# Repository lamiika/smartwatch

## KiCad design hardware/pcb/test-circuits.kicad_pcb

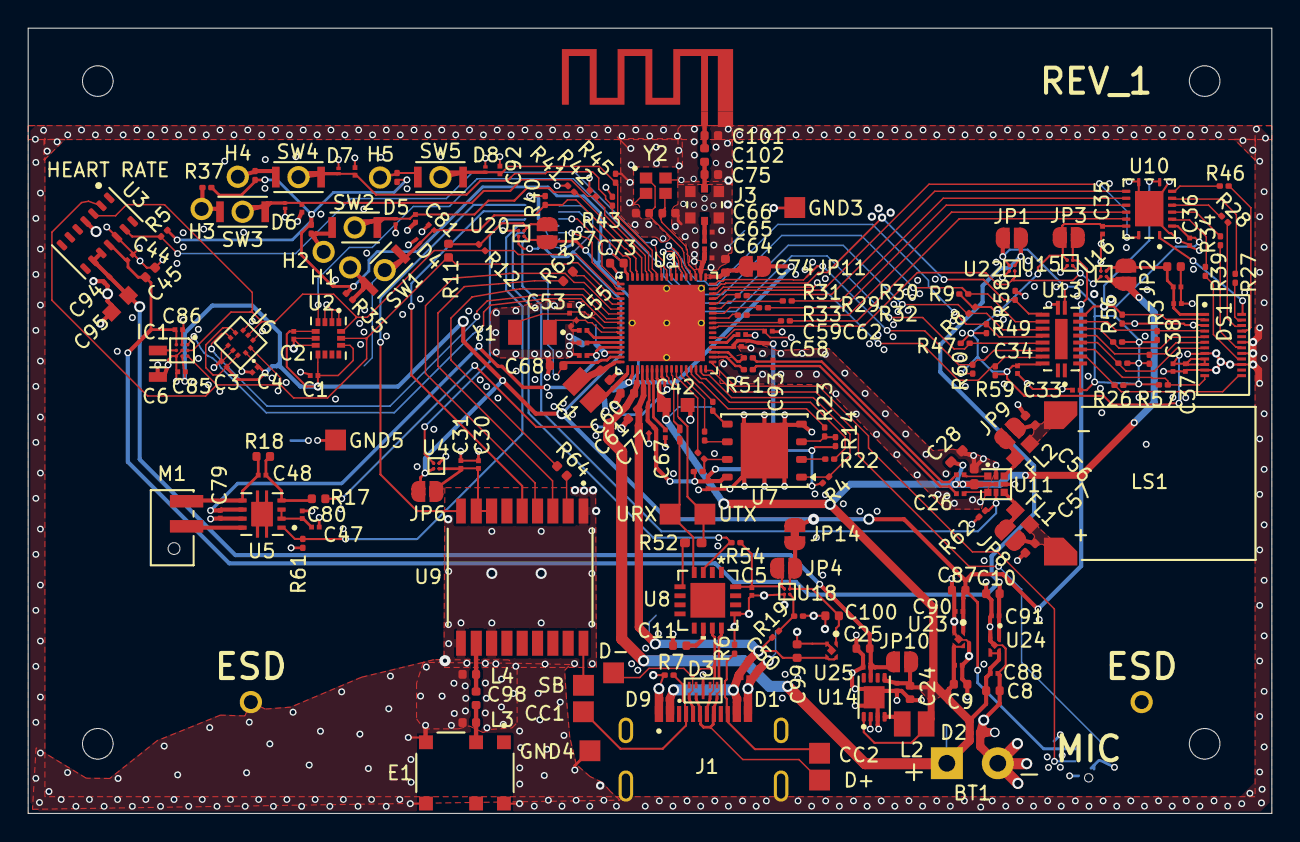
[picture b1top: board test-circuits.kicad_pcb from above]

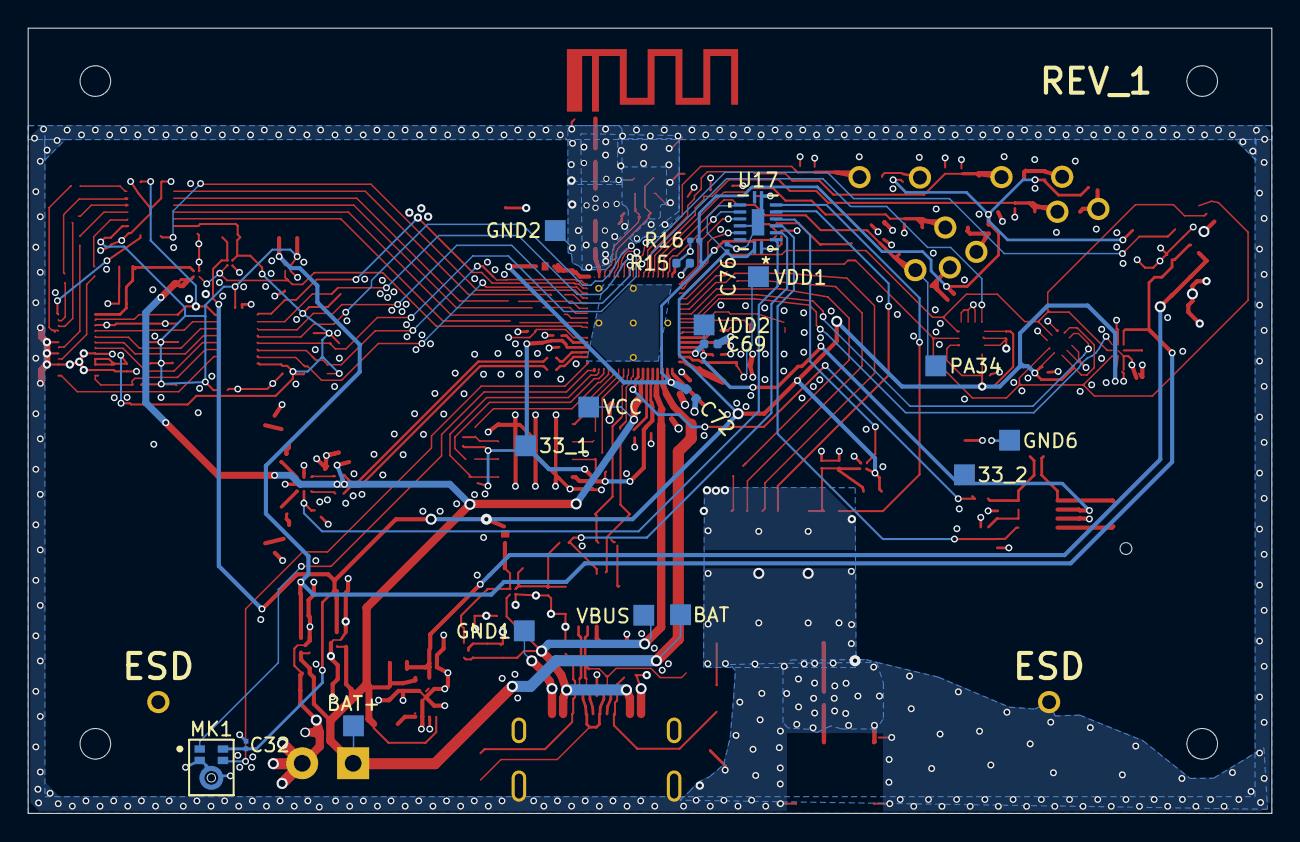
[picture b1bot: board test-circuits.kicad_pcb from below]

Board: 4 copper layers, 89.3 x 56.4 mm, 242 parts (20 on the bottom side), 146 nets.

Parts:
33_1, 33_2: TestPoint_Square; TestPoint_Pad_1.5x1.5mm
BAT: TestPoint_Square; TestPoint_Pad_1.5x1.5mm
BAT+: TestPoint_Square; TestPoint_Pad_1.5x1.5mm
BT1: Battery_Cell; Battery_LiPo_wire_leads
C1, C2, C5, C23, C30, C33, C34, C35, C36, C37, C38, C39, C44, C49, C76, C77, C78, C79, C81, C82, C83, C84, C92: 100nF_0201; C_0201_TightCourtyard
C3, C4: 100n; C_0201_TightCourtyard
C6: 2.2uF_0402_6.3V; C_0805
C8, C9, C10, C87, C99, C100: 1uF_0402_25V; C_0402
C11: 0.22uF; C_0402_1005Metric
C24, C25: 10uF 0402 X7R; C_0402_1005Metric
C26, C27: 1nF_0201_4V; C_0201_TightCourtyard
C28: 10u; C_0402_1005Metric_Pad0.74x0.62mm_HandSolder
C29: 1u; C_0402_1005Metric_Pad0.74x0.62mm_HandSolder
C31, C32, C41, C59, C62, C71: 1uF_0201_4V; C_0201_TightCourtyard
C40, C45, C46, C68, C69, C72, C73, C74: 4.7uF_0402_6.3V; C_0402
C42, C95: 10uF_0603_10V; C_0603
C47, C48: 10nF_0201; C_0201_TightCourtyard
C50, C61: 10uF; C_0402_1005Metric
C52, C54: 1.2pF; C_0402_1005Metric
C53, C55: 1.2pF; C_0201_TightCourtyard
C56, C57: 200pF; C_0402_1005Metric
C58, C67: 2.2uF_0201_10V; C_0201_TightCourtyard
C60: 4.7uF_0402_10V; C_0402
C64, C65, C66: 15pF_0201; C_0201_TightCourtyard
C70: 470nF; C_0201_TightCourtyard
C75, C101, C102: 15pF_0201; C_0402
C80: 1nF_0201; C_0201_TightCourtyard
C85, C86, C94, C96, C97: 100nF_0201_X7R; C_0201_TightCourtyard
C88, C89, C90, C91: 100nF_0201_X0G; C_0201_TightCourtyard
C93: 1.5nF_0201; C_0201_TightCourtyard
C98: 1.5pF_0402_50V; C_0402
CC1, CC2: TestPoint_Square; TestPoint_Pad_1.5x1.5mm
D1, D2, D4, D5, D6, D7, D8, D9: ESD_BD_CL6.5pF; ESD200_B1_CSP0201
D3: PUSB3BB4; PUSB3BB4_DFN2510A10
D+: TestPoint_Square; TestPoint_Pad_1.5x1.5mm
D-: TestPoint_Square; TestPoint_Pad_1.5x1.5mm
DS1: GLO132-D-M2003; GLO132-D-M2003_OK-03F024-04
E1: SR4G008; XCVR_SR4G008
ESD: MountingHole_Pad_1.0mm; TH_1.0mm_Pad1.6mm
ESD#2: MountingHole_Pad_1.0mm; TH_1.0mm_Pad1.6mm
FL1, FL2: BLM18PG121SN1D; BEADC1608X95N
GND1, GND2, GND3, GND4, GND5, GND6: TestPoint_Square; TestPoint_Pad_1.5x1.5mm
H1, H2, H3, H4, H5: MountingHole_Pad_1.2mm; TH_1.0mm_Pad1.6mm
IC1: BMM350; BGA9C40P3X3_128X128X54
J1: UJ20-C-H-G-MSMT-2B-P16-TR; SAMESKY_UJ20-C-H-G-MSMT-2B-P16-TR
J3: MM8130-2600RA2; MURATA_MM8130-2600RA2
JP1, JP2, JP3, JP4, JP6, JP7, JP8, JP9, JP10: SolderJumper_2_Open; SolderJumper-2_P1.3mm_Open_RoundedPad1.0x1.5mm
JP11, JP14: SolderJumper_2_Bridged; SolderJumper-2_P1.3mm_Bridged_RoundedPad1.0x1.5mm
L1, L2: MLP2016H4R7MT0S1; INDC2016X100N
L3, L4: 12nH; 0402
LS1: CMS-151125-18S-X8; SPKR_CMS-151125-18S-X8
M1: Motor_AC; VLV041235L
MK1: IM68D121JV01XTMA1; IFX-PG-TLGA-5N-9-V
PA34: TestPoint_Square; TestPoint_Pad_1.5x1.5mm
R3, R8, R9, R13: res_2.2k_0201; R_0201_0603Metric
R4, R10, R14, R19, R25, R26, R47, R48, R49, R56, R57, R58, R59, R60, R61, R62: 100k_0201; R_0201_0603Metric
R5, R16, R40, R41, R42, R43, R45, R54: 10k_0201; R_0201_0603Metric
R6, R7, R35, R36, R37, R38, R44: 5.1k_0201; R_0201_0603Metric
R11: 2.2k_0402; R_0402
R12: 2.2k_0201; R_0201_0603Metric
R15: 10k; R_0402
R17: 100k_0402; R_0402
R18: 68k_0402; R_0402
R20: 1M_0201; R_0201_0603Metric
R21, R22, R23, R24, R55: 33R_0201; R_0201_0603Metric
R27, R28, R34, R39, R46: 0R_0201; R_0201_0603Metric
R29, R30, R31, R32, R33: 100R_0201; R_0201_0603Metric
R50, R51: 1.0k_0201; R_0201_0603Metric
R52: 100R_0201; R_0402_1005Metric_Pad0.72x0.64mm
R53: 100R_0201; R_0201_0603Metric_Pad0.64x0.40mm
R63, R64: 33R_0402; R_0402
SB: TestPoint_Square; TestPoint_Pad_1.5x1.5mm
SW1, SW2, SW3, SW4, SW5: TL3780AF100QG; TL3780AF100QG-through-holes
U1: SF32LB52xUx; ArtInChip_0.2_QFN-68-1EP_7x7mm_P0.35mm_EP5.49x5.49mm
U2: LSM6DSV16XTR; XDCR_LSM6DSV16XTR
U3: MAX30101EFD; PSON80P560X330X165-14N
U4, U15, U16, U18, U20, U22: TCK127BG_LF; WCSP4G_TOS
U5: DRV8601DRBR; IC_DRV8601DRBT
U6: BMP581
U7: XT25F128FWOIGT-W; WSON-8-1EP_6x5mm_P1.27mm_EP3.4x4mm
U8: MCP2221A-I/ML; QFN16_ML_MCH
U9: MAX-M10M-00B; XCVR_MAX-M10M-00B
U10: TXB0606RGYR; VQFN-16_RGY0016A_TEX
U11: PAM8013AKR
U13: NXS0108BQX; IC_NXS0108BQX
U14: DIO6605BFN8; DIO6605BFN8_DFN2x3_8EP
U17: 74HC595BQ,115; DHVQFN16_SOT763-1_NEX
U23, U25: MIC5317-3.3YMT-TZ; VREG_MIC5317-3.3YMT-TZ
U24: MIC5365-1.8YMT-TZ; VREG_MIC5365-1.8YMT-TZ
URX: TestPoint_Square; TestPoint_Pad_1.5x1.5mm
UTX: TestPoint_Square; TestPoint_Pad_1.5x1.5mm
VBUS: TestPoint_Square; TestPoint_Pad_1.5x1.5mm
VCC: TestPoint_Square; TestPoint_Pad_1.5x1.5mm
VDD1, VDD2: TestPoint_Square; TestPoint_Pad_1.5x1.5mm
Y1: SF32K32768D71T01; SF32K32768D71T01_3215
Y2: SX20Y048000B31T004; SX20Y048000B31T004_2016

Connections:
+1V8: C10.1, C44.1, C45.1, C86.2, C91.1, IC1.C1 (VDD), JP1.2 (B), U3.11 (VDD), U22.A2 (VIN), U24.1 (VOUT)
+3V3: C1.1, C2.1, C3.1, C4.1, C32.2, C76.2, C85.2, C87.1, C90.1, IC1.B3 (VDDIO), JP3.2 (B), JP6.2 (B), JP14.2 (B), MK1.5 (VDD), U2.5 (VDD_IO), U2.8 (VDD), U2.12 (CS), U4.A2 (VIN), U6.1 (VDDIO), U6.6 (CSB), U6.10 (VDD), U15.A2 (VIN), U17.10 (*MR), U17.16 (VCC), U23.1 (VOUT)
/Connector/3V3: C100.1, JP4.2 (B), JP14.1 (A), U18.A2 (VIN), U25.1 (VOUT)
/Connector/D+: D3.2 (CH2), D3.5 (CH4), D+.1 (1_1), J1.A6 (DP1), J1.B6 (DP2), U8.12 (D+)
/Connector/D-: D3.1 (CH1), D3.4 (CH3), D-.1 (1_1), J1.A7 (DN1), J1.B7 (DN2), U8.11 (D-)
/Connector/DBG_*RST: R54.2, U8.3 (*RST), U17.3 (Q3)
/Connector/DBG_UART_RXD: R53.2, U8.4 (URX), URX.1 (1_1)
/Connector/DBG_UART_TXD: R52.1, U1.27 (PA18), UTX.1 (1_1)
/Connector/VDD: C5.2, JP4.1 (A), R54.1, U8.16 (VDD), U18.A1 (VOUT)
/Display Module/1V8_circuit: C33.2, C36.2, JP1.1 (A), R3.1, R13.1, R25.1, R26.2, R48.1, R57.2, U10.2 (VCCA), U13.2 (VCC_A), U13.10 (OE), U22.A1 (VOUT)
/Display Module/3V3_circuit: C34.2, C35.2, C37.1, C38.1, DS1.9 (VDD33), DS1.10 (VDD33), JP3.1 (A), R8.1, R9.1, R47.1, R49.1, R59.2, R60.2, U10.15 (VCCB), U13.19 (VCC_B), U15.A1 (VOUT)
/Display Module/DISPLAY_SI00: R30.2, U1.46 (PA5)
/Display Module/DISPLAY_SI01: R29.2, U1.45 (PA6)
/Display Module/DISPLAY_SI02: R33.2, U1.44 (PA7)
/Display Module/DISPLAY_SI03: R32.2, U1.43 (PA8)
/Display Module/DISPLAY_SPI_CLK: R31.2, U1.47 (PA4)
/Display Module/DISPLAY_SPI_CS: U1.48 (PA3), U10.16 (B1)
/Display Module/LOAD_DISPLAY: U1.42 (PA9), U15.B2 (CONTROL), U16.B2 (CONTROL), U22.B2 (CONTROL)
/Display Module/RESET_1V8: DS1.12 (RESET), R57.1, U13.4 (A3)
/Display Module/VCI_EN_1V8: DS1.2 (VCI_EN), R56.1, U10.8 (OE), U13.9 (A8)
/Display Module/i_INT: R47.2, U1.57 (PA43), U13.16 (B4)
/Display Module/i_RESET: R60.1, U1.51 (PA0), U13.17 (B3)
/Display Module/i_RST: R49.2, U1.56 (PA44), U13.15 (B5)
/Display Module/i_SCL: R9.2, U1.58 (PA42), U13.13 (B7)
/Display Module/i_SDA: R8.2, U1.59 (PA41), U13.14 (B6)
/Display Module/i_TE: R59.1, U1.49 (PA2), U13.18 (B2)
/Display Module/i_VCI_EN: R58.1, U1.50 (PA1), U13.12 (B8)
/Display Module/t_INT: DS1.7 (TP_INT), R25.2, U13.5 (A4)
/Display Module/t_RST: DS1.6 (TP_RST), R48.2, U13.6 (A5)
/Display Module/t_SCL: DS1.4 (TP_SCL), R3.2, U13.8 (A7)
/Display Module/t_SDA: DS1.5 (TP_SDA), R13.2, U13.7 (A6)
/Display Module/t_TE: DS1.13 (TE), R26.1, U13.3 (A2)
/Flash Storage/FLASH CS#: R4.2, U1.33 (PA12), U7.1 (CS#)
/Flash Storage/FLASH IO0: R21.2, U1.30 (PA15)
/Flash Storage/FLASH IO1: R22.2, U1.32 (PA13)
/Flash Storage/FLASH IO2: R23.2, U1.31 (PA14)
/Flash Storage/FLASH IO3: R24.2, U1.28 (PA17)
/Flash Storage/FLASH SCK: R55.1, U1.29 (PA16)
/GNSS/GNSS_EXTINT: U9.5 (EXTINT), U17.6 (Q6)
/GNSS/GNSS_RESET: U9.9 (~RESET), U17.7 (Q7)
/GNSS/GNSS_RXD: R63.1, U9.3 (RXD)
/GNSS/GNSS_TIMEPULSE: U1.6 (PA27), U9.4 (TIMEPULSE)
/GNSS/GNSS_TXD: R64.1, U1.7 (PA26)
/GNSS/LOAD_GNSS: U4.B2 (CONTROL), U17.5 (Q5)
/Heart Rate PPG/INT_PPG: R5.2, U1.60 (PA40), U3.13 (~INT)
/IMU/INT1_IMU: U1.61 (PA39), U2.4 (INT1)
/MCU/48-1: C52.1, U1.55 (XTAL48M_XI), Y2.1 (XTAL1)
/MCU/48-2: C54.1, U1.54 (XTAL48M_XO), Y2.3 (XTAL2)
/MCU/ANT: C64.1, C65.1, U1.53 (ANT)
/MCU/AVDD_BRF: C74.2, JP11.1 (A), U1.52 (AVDD_BRF)
/MCU/BT_ANT_MATCHING: C75.1, C102.1, J3.2 (OUT)
/MCU/BT_ANT_TRACE: C101.1, C102.2
/MCU/BUCK_FB: C46.2, L1.2, U1.17 (BUCK_FB)
/MCU/BUCK_LX: L1.1, U1.18 (BUCK_LX)
/MCU/CLK_MK: MK1.4 (CLK), U1.35 (PA10)
/MCU/DATA_MK: MK1.1 (DATA), U1.34 (PA11)
/MCU/DS: U1.2 (PA31), U17.14 (DS)
/MCU/GPADC_VREF: C73.2, R15.2, R16.2, U1.68 (GPADC_VREF)
/MCU/INT_BARO: U1.8 (PA25), U6.7 (INT)
/MCU/INT_MAGN: IC1.A1 (INT), U1.9 (PA24)
/MCU/LOAD_I2C_S: U17.1 (Q1), U20.B2 (CONTROL)
/MCU/LRA_EN: R61.2, U5.1 (EN), U17.4 (Q4)
/MCU/LRA_IN1: R17.1, U1.25 (PA20)
/MCU/MIC_BIAS: C62.1, U1.40 (MIC_BIAS)
/MCU/SD_SPEAKER: R62.1, U11.8 (SD), U17.2 (Q2)
/MCU/SHCP: U1.67 (PA33), U17.11 (SHCP)
/MCU/SPEAKER_N: C26.1, C93.1, R51.2
/MCU/SPEAKER_P: C27.1, C93.2, R50.2
/MCU/STCP: U1.1 (PA32), U17.12 (STCP)
/MCU/VDD18_VOUT: C67.1, U1.23 (VDD18_VOUT)
/MCU/VDD_RET: C70.1, U1.13 (VDD_RET)
/MCU/VDD_RTC: C71.1, U1.12 (VDD_RTC)
/MCU/VDD_VOUT1: C68.1, U1.16 (VDD_VOUT1), VDD1.1 (1_1)
/MCU/VDD_VOUT2: C69.1, U1.15 (VDD_VOUT2), VDD2.1 (1_1)
/MCU/dac+: R50.1, U1.37 (DACP)
/MCU/dac-: R51.1, U1.36 (DACN)
/MCU/sw1: C81.2, D4.2, PA34.1 (1_1), R40.1, SW1.1, U1.66 (PA34)
/MCU/sw2: C82.2, D5.2, R41.1, SW2.1, U1.65 (PA35)
/MCU/sw3: C83.2, D6.2, R42.1, SW3.1, U1.64 (PA36)
/MCU/sw4: C84.2, D7.2, R43.1, SW4.1, U1.63 (PA37)
/MCU/sw5: C92.2, D8.2, R45.1, SW5.1, U1.62 (PA38)
/SCL_S: IC1.A3 (SCK), R11.2, U1.4 (PA29), U2.13 (SCL), U3.2 (SCL), U6.2 (SCK)
/SDA_S: IC1.A2 (SDA), R12.2, U1.3 (PA30), U2.14 (SDA), U3.3 (SDA), U6.4 (SDI)
/Speaker/IN+: C27.2, U11.1 (INP)
/Speaker/IN-: C26.2, U11.7 (INN)
BAT: BAT.1 (1_1), BAT+.1 (1_1), BT1.1 (+), C8.1, C9.1, C24.1, C28.1, C29.1, C42.1, C60.1, C88.1, C89.1, C96.1, D2.2, JP2.2 (B), JP10.1 (A), L2.1, U1.20 (BAT), U1.24 (VCC), U11.4 (VDD), U11.5 (VDD), U14.1 (EN), U14.5 (VIN), U16.A2 (VIN), U23.3 (EN), U23.4 (VIN), U24.3 (EN), U24.4 (VIN), VCC.1 (1_1)
GND: BT1.2 (-), C1.2, C2.2, C3.2, C4.2, C5.1, C6.2, C8.2, C9.2, C10.2, C11.2, C23.2, C24.2, C25.2, C28.2, C29.2, C30.2, C31.2, C32.1, C33.1, C34.1, C35.1, C36.1, C37.2, C38.2, C39.2, C40.2, C41.2, C42.2, C44.2, C45.2, C46.1, C47.1, C49.1, C50.2, C52.2, C53.2, C54.2, C55.2, C56.1, C57.1, C58.1, C59.1, C60.2, C61.2, C62.2, C65.2, C66.2, C67.2, C68.2, C69.2, C70.2, C71.2, C72.2, C73.1, C74.1, C75.2, C76.1, C77.1, C78.1, C79.1, C80.1, C81.1, C82.1, C83.1, C84.1, C85.1, C86.1, C87.2, C88.2, C89.2, C90.2, C91.2, C92.1, C94.2, C95.2, C96.2, C97.2, C99.2, C100.2, C101.2, D1.1, D2.1, D3.3 (GND), D3.9 (GND), D4.1, D5.1, D6.1, D7.1, D8.1, D9.1, DS1.3 (GND), DS1.8 (GND), DS1.11 (GND), DS1.15 (GND), DS1.17 (GND), DS1.19 (GND), E1.3, E1.4, E1.6, ESD.1 (1_1), ESD#2.1 (1_1), GND1.1 (1_1), GND2.1 (1_1), GND3.1 (1_1), GND4.1 (1_1), GND5.1 (1_1), GND6.1 (1_1), IC1.B1 (GND), IC1.B2 (ADSEL), IC1.C3 (BYPASS), J1.A1/B12 (GND), J1.B1/A12 (GND__1), J1.SH1 (SHIELD), J1.SH2 (SHIELD__1), J1.SH3 (SHIELD__2), J1.SH4 (SHIELD__3), J3.G1 (GND), J3.G2 (GND__1), J3.G3 (GND__2), J3.G4 (GND__3), L3.1, L4.1, MK1.2 (LR), MK1.3 (GND), R6.2, R7.2, R15.1, R20.2, R40.2, R41.2, R42.2, R43.2, R45.2, R56.2, R58.2, R61.1, R62.2, U1.69, U2.1 (SDO/SA0), U2.2 (SDX/AH1/QVAR1), U2.3 (SCX/AH2/QVAR2), U2.6 (GND), U2.7 (GND), U3.4 (PGND), U3.12 (GND), U4.B1 (GND), U5.7 (GND), U6.3 (VSS_1), U6.5 (SDO), U6.8 (VSS_2), U6.9 (VSS_3), U7.4 (VSS), U7.9 (EPAD), U8.13 (VSS), U9.1 (GND), U9.10 (GND__1), U9.12 (GND__2), U10.9 (GND), U10.17 (EPAD), U11.2 (GND), U11.6 (GND), U13.11 (GND), U14.2 (AGND), U14.3 (PGND), U14.9 (GND_PAD), U15.B1 (GND), U16.B1 (GND), U17.8 (GND), U17.13 (*OE), U17.17 (GND), U18.B1 (GND), U20.B1 (GND), U22.B1 (GND), U23.2 (GND), U23.5 (EPAD), U24.2 (GND), U24.EP (EXP), U25.2 (GND), U25.5 (EPAD), Y2.2 (GND), Y2.4 (GND)
unnamed: C98.1, E1.2, L3.2
unnamed: DS1.23 (SIO0_MOSI_SDA), R27.1
unnamed: DS1.22 (SIO1_MISO), R28.1
unnamed: DS1.18 (SIO2), R34.1
unnamed: DS1.16 (SIO3), R39.1
unnamed: DS1.21 (SPI_CLK), R46.2
unnamed: DS1.24 (SPI_CS), U10.1 (A1)
unnamed: C39.1, C40.1, C41.1, DS1.1 (VBAT), JP2.1 (A), U16.A1 (VOUT)
unnamed: H1.1 (1_1), R35.2, SW1.2
unnamed: H2.1 (1_1), R36.2, SW2.2
unnamed: H3.1 (1_1), R37.2, SW3.2
unnamed: H4.1 (1_1), R38.2, SW4.2
unnamed: H5.1 (1_1), R44.2, SW5.2
unnamed: C6.1, IC1.C2 (CRST)
unnamed: CC1.1 (1_1), J1.A5 (CC1), R7.1
unnamed: CC2.1 (1_1), J1.B5 (CC2), R6.1
unnamed: C64.2, C66.1, J3.1 (IN)
unnamed: C30.1, C31.1, JP6.1 (A), U4.A1 (VOUT), U9.7 (V_IO), U9.8 (VCC)
unnamed: JP7.2 (B), R11.1, R12.1, U20.A1 (VOUT)
unnamed: C57.2, FL1.2, JP8.1 (A), LS1.P
unnamed: FL1.1, JP8.2 (B), U11.9 (OUTP)
unnamed: FL2.1, JP9.1 (A), U11.3 (OUTN)
unnamed: C56.2, FL2.2, JP9.2 (B), LS1.N
unnamed: C59.2, U1.39 (AUD_VREF)
unnamed: R53.1, U1.26 (PA19)
unnamed: C55.1, U1.11 (PA22), Y1.1
unnamed: C53.1, U1.10 (PA23), Y1.2
unnamed: R63.2, U1.5 (PA28)
unnamed: C48.2, R17.2, R18.1, U5.4 (IN1)
unnamed: C47.2, C80.2, U5.2 (REFOUT), U5.3 (IN2)
unnamed: C48.1, M1.2, R18.2, U5.5 (OUT+)
unnamed: M1.1, U5.8 (OUT-)
unnamed: R10.2, R24.1, U7.7 (HOLD#/RESET#/IO3)
unnamed: R55.2, U7.6 (SCLK)
unnamed: R21.1, U7.5 (SI/IO0)
unnamed: R22.1, U7.2 (SO/IO1)
unnamed: R14.2, R23.1, U7.3 (WP#/IO2)
unnamed: R52.2, U8.5 (UTX)
unnamed: C11.1, U8.10 (VUSB)
unnamed: C98.2, L4.2, U9.11 (RF_IN)
unnamed: R64.2, U9.2 (TXD)
unnamed: SB.1 (1_1), U9.18 (~SAFEBOOT)
unnamed: R39.2, U10.3 (A2)
unnamed: R34.2, U10.4 (A3)
unnamed: R28.2, U10.5 (A4)
unnamed: R27.2, U10.6 (A5)
unnamed: R46.1, U10.7 (A6)
unnamed: R32.1, U10.14 (B2)
unnamed: R33.1, U10.13 (B3)
unnamed: R29.1, U10.12 (B4)
unnamed: R30.1, U10.11 (B5)
unnamed: R31.1, U10.10 (B6)
unnamed: L2.2, U14.4 (SW)
unnamed: R19.2, R20.1, U18.B2 (CONTROL)
VBUS: C49.2, C50.1, C61.1, C99.1, D1.2, D9.2, J1.A4/B9 (VBUS), J1.B4/A9 (VBUS__1), R19.1, U1.21 (VBUS), U25.3 (EN), U25.4 (VIN), VBUS.1 (1_1)
VDD33_VOUT1: 33_1.1 (1_1), C23.1, C58.2, C77.2, R4.1, R10.1, R14.1, U1.22 (VDD33_VOUT1), U1.38 (AVDD33_AUD), U7.8 (VCC)
VDD33_VOUT2: 33_2.1 (1_1), C78.2, C79.2, U1.14 (VDD33_VOUT2), U5.6 (VDD)
VLED+: C25.1, C94.1, C95.1, C97.1, JP10.2 (B), U3.9 (VLED+), U3.10 (VLED+), U14.7 (VOUT)
VSYS: C72.1, JP7.1 (A), JP11.2 (B), R5.1, R16.1, R35.1, R36.1, R37.1, R38.1, R44.1, U1.19 (VSYS), U20.A2 (VIN)
